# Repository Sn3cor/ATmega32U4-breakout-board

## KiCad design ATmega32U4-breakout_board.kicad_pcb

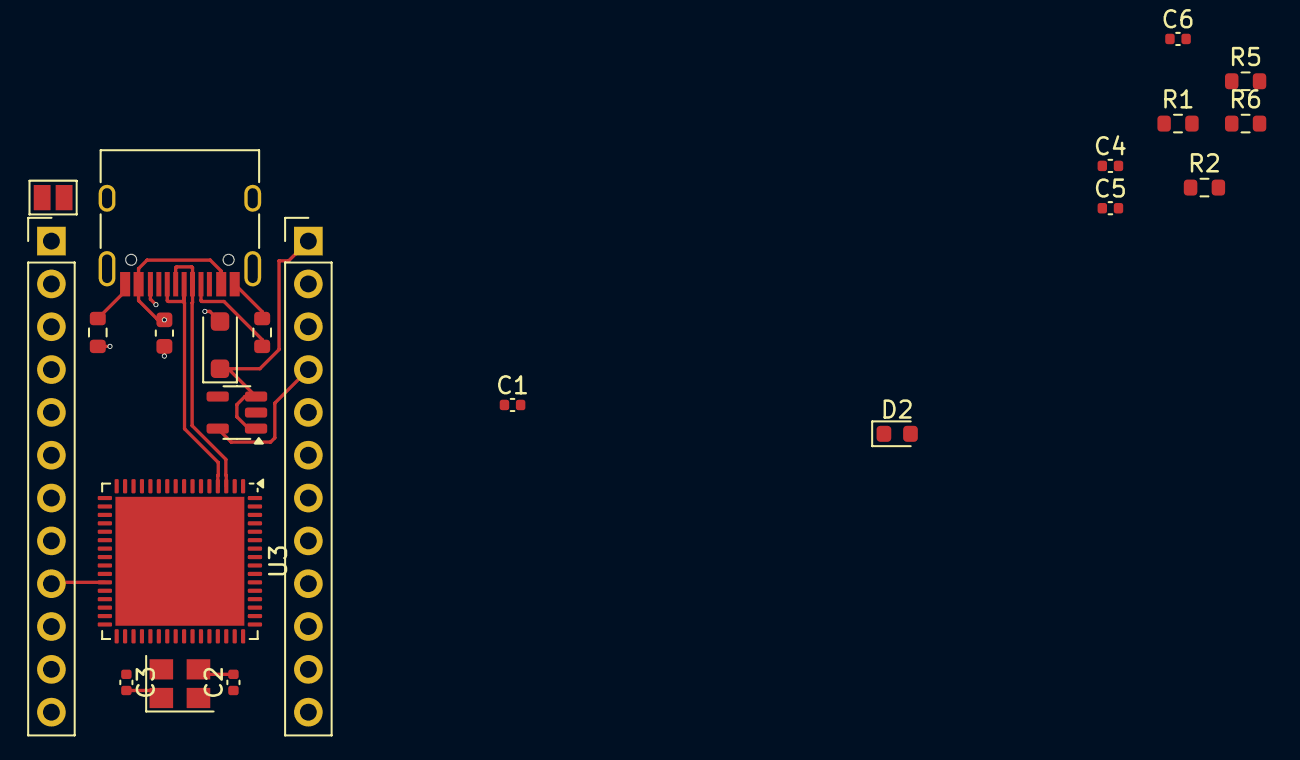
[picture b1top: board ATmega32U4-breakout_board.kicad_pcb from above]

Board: 2 copper layers, 22 parts (0 on the bottom side), 32 nets.

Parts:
C1, C5: 1uF; C_0402_1005Metric
C2, C3: 22pF; C_0402_1005Metric
C4: 0.1uF; C_0402_1005Metric
C6: 10uF; C_0402_1005Metric
D1: D_SOD-123F
D2: LED; LED_0603_1608Metric
F1: 500mA; Fuse_0603_1608Metric
J1: USB_C_Receptacle_USB2.0_16P; USB_C_Receptacle_HRO_TYPE-C-31-M-12
J2, J3: Conn_01x12; PinHeader_1x12_P2.54mm_Vertical
JP1: VCC jumper; SolderJumper-2_P1.3mm_Open_Pad1.0x1.5mm
R1, R2: 22; R_0603_1608Metric
R3, R4: 5.1k; R_0603_1608Metric
R5: 330; R_0603_1608Metric
R6: 10k; R_0603_1608Metric
U2: MIC5219-3.3YM5; SOT-23-5
U3: ATmega32U4-M; QFN-64-1EP_9x9mm_P0.5mm_EP7.65x7.65mm
Y1: Crystal_GND24; Crystal_SMD_3225-4Pin_3.2x2.5mm

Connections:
+5V: F1.1, J1.A4 (VBUS), J1.A9 (VBUS), J1.B4 (VBUS), J1.B9 (VBUS), U3.2 (UVCC), U3.7 (VBUS)
/B1: J3.9, U3.9 (PB1)
/B2: J3.11, U3.10 (PB2)
/B3: J3.10, U3.11 (PB3)
/B4: J2.11, U3.28 (PB4)
/B5: J2.12, U3.29 (PB5)
/B6: J3.12, U3.30 (PB6)
/C6: J2.8, U3.31 (PC6)
/D0: J2.6, U3.18 (PD0)
/D1: J2.5, U3.19 (PD1)
/D2: J2.2, U3.20 (PD2)
/D3: J2.1, U3.21 (PD3)
/D4: J2.7, U3.25 (PD4)
/D7: J2.9, U3.27 (PD7)
/D+: J1.A6 (D+), J1.B6 (D+), R1.2, U3.4 (D+)
/D-: J1.A7 (D-), J1.B7 (D-), R2.2, U3.3 (D-)
/E6: J2.10, U3.1 (PE6)
/F4: J3.5, U3.39 (PF4)
/F5: J3.6, U3.38 (PF5)
/F6: J3.7, U3.37 (PF6)
/F7: J3.8, U3.36 (PF7)
/RAW: D1.1 (K), J3.1, U2.1 (IN), U2.3 (EN)
/RESET: J3.3, R6.2, U3.13 (~RESET)
GND: C1.2, C2.1, C3.1, C4.2, C5.2, C6.2, D2.1 (K), J1.A1 (GND), J1.A12 (GND), J1.B1 (GND), J1.B12 (GND), J2.3, J2.4, J3.2, R3.2, R4.2, U2.2 (GND), U3.5 (UGND), U3.15 (GND), U3.23 (GND), U3.35 (GND), U3.43 (GND), U3.45 (GND), Y1.2, Y1.4
unnamed: D1.2 (A), F1.2, JP1.1 (A)
unnamed: D2.2 (A), R5.2
unnamed: J1.A5 (CC1), R3.1
unnamed: J1.B5 (CC2), R4.1
unnamed: C1.1, U3.6 (UCAP)
unnamed: C2.2, U3.17 (XTAL1), Y1.3
unnamed: C3.2, U3.16 (XTAL2), Y1.1
VCC: C4.1, C5.1, C6.1, J3.4, JP1.2 (B), R5.1, R6.1, U2.5 (OUT), U3.14 (VCC), U3.24 (AVCC), U3.34 (VCC), U3.44 (AVCC)

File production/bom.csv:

Designator,Footprint,Quantity,Value,LCSC Part #
"C1, C5",0603,2,1u,
"C2, C3",0603,2,22p,
C4,0603,1,0.1u,
C6,0603,1,10u,
D1,D_SOD-123F,1,D_Schottky,
D2,0603,1,LED,
F1,0603,1,500mA,
J1,USB_C_Receptacle_HRO_TYPE-C-31-M-12,1,USB_C_Receptacle_USB2.0_16P,
"J2, J3",PinHeader_1x12_P2.54mm_Vertical,2,Conn_01x12,
"R1, R2",0603,2,22,
"R3, R4",0603,2,5.1k,
R5,0603,1,330,
R6,0603,1,10k,
U1,TQFP-44_10x10mm_P0.8mm,1,ATmega32U4-A,
U2,SOT-23-5,1,MIC5219-3.3YM5,
Y1,Crystal_SMD_3225-4Pin_3.2x2.5mm,1,Crystal_GND24,

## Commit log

2025-04-15 initialize repo
2025-04-18 added usb and voltage regulator
2025-04-18 generated additional files
2025-04-19 schematic fix + start of pcb designing
2025-04-22 small update
2025-04-25 changed pcb v1
